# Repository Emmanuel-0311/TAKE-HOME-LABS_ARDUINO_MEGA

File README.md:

# Take-Home Labs: Laboratorios con Arduino Mega (ATmega2560)

## Introducción
Este repositorio contiene una serie de prácticas de laboratorio diseñadas para el autoaprendizaje y la experimentación en casa, enfocadas en la arquitectura del microcontrolador ATmega2560. Además, se empleó KiCad para el diseño de una shield personalizada, en la cual se integran tres plantas (electrónica, cinemática y de visualización) que permiten validar e implementar diferentes estrategias de control y adquisición de señales.

## Objetivo General
Desarrollar competencias en programación de sistemas embebidos utilizando la plataforma Arduino Mega, priorizando el control directo del hardware, así como la integración y validación de plantas físicas diseñadas en KiCad mediante una shield personalizada.

## Descipción de las plantas
**Planta 1**: Planta electrónica basada en el CD4066, utilizada para la conmutación y enrutamiento de señales analógicas mediante interruptores controlados digitalmente. Integra redes RC en cascada que permiten modificar la dinámica del sistema, ajustando su respuesta según las etapas activadas.
**Planta 2:** Planta electromecánica basada en un motor DC N20 con encoder de cuadratura, donde la señal PWM controla la velocidad mediante un MOSFET.
El encoder proporciona retroalimentación de posición y velocidad, permitiendo implementar sistemas de control en lazo cerrado.
**Planta 3:** Planta electrónica basada en el LM3914N, utilizada para visualizar una señal analógica mediante una barra de LEDs proporcional al nivel de voltaje.
Incorpora un filtro pasa-bajas RC que suaviza la señal de entrada (PWM), permitiendo una lectura estable y continua en la visualización.

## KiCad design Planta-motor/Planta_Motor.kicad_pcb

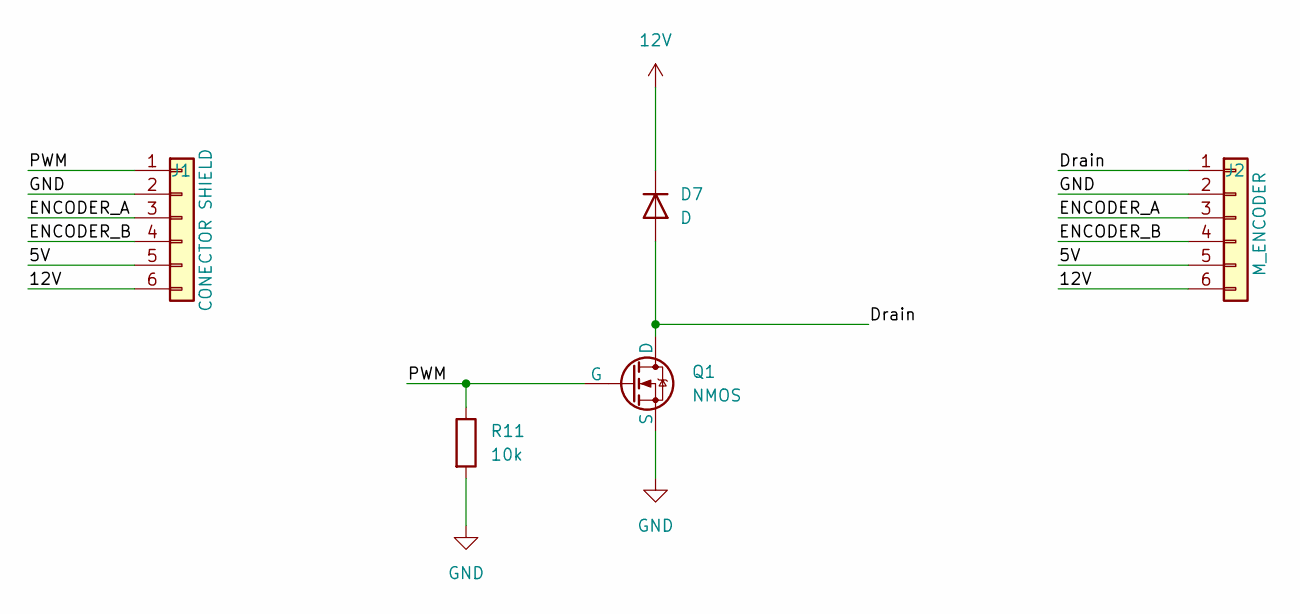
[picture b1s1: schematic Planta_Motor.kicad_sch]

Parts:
D7: D; D_DO-41_SOD81_P10.16mm_Horizontal
J1: CONECTOR SHIELD; PinHeader_1x06_P2.54mm_Vertical
J2: M_ENCODER; JST_XH_B6B-XH-A_1x06_P2.50mm_Vertical
Q1: NMOS; TO-220-3_Vertical
R11: 10k; R_Axial_DIN0207_L6.3mm_D2.5mm_P10.16mm_Horizontal

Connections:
12V: D7.1 (K), J1.6, J2.6
/5V: J1.5, J2.5
/Drain: D7.2 (A), J2.1, Q1.1 (D)
/ENCODER_A: J1.3, J2.3
/ENCODER_B: J1.4, J2.4
/PWM: J1.1, Q1.2 (G), R11.1
GND: J1.2, J2.2, Q1.3 (S), R11.2

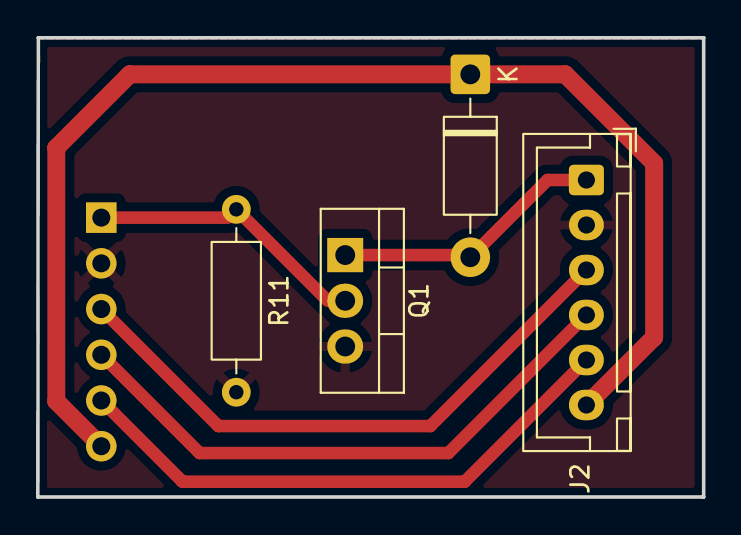
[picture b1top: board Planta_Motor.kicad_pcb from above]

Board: 2 copper layers, 37.0 x 25.5 mm, 5 parts (1 on the bottom side), 7 nets.

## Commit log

2026-04-24 Create a
2026-04-24 Create Materiales
